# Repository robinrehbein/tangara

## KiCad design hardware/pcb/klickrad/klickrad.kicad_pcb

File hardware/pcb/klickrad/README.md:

# Klickrad-Modul v2 (KiCad 9)

Runde Platine (Ø 32 mm, **0,8 mm** (1,0 mm als Alternative), **2 Lagen**) mit Touch-Rad, kapazitiver Mitteltaste, Guard-Kanal, Haptik-Treiber und Lötpads für den aufgeklebten LRA. Touch-Controller **AT42QT2120** (I²C 0x1C, Wheel-Modus), Haptik **DRV2605L** (0x5A): Schaltung, Elektrodenform und Firmware-Belegung stammen so weit wie möglich von der **Tangara-Faceplate** (cool tech zone). Schnittstelle und Maße folgen `TEILE.md`, Abschnitt „Klickrad-Modul“, mit den unten genannten Abweichungen.

Stand: 2026-10-05, Revision 2 (v1 mit MPR121 bleibt in der git-Historie; 2026-10-05: J1-Footprint, Steckerausrichtung und LRA-Freifläche nach `docs/REVIEW-HAUPTPLATINE.md` K1/H6 geändert, neu geroutet). Erstellt und geprüft mit KiCad 9.0.9 (`kicad-cli`) im Container. **Nichts davon wurde an echter Hardware getestet.**

## Lizenz und Herkunft

Dieses Modul übernimmt Schaltung, Elektrodengeometrie (als Algorithmus), Symbol und Pinbelegung aus der Tangara-Faceplate (`tangara-hw/tangara-faceplate`, `tangara-hw/touchwheel-cover`) von **cool tech zone** (https://cooltech.zone/tangara/), lizenziert unter **CERN-OHL-S-2.0**. Das Modul ist deshalb ebenfalls **CERN-OHL-S-2.0** (Lizenztext: `LICENSE` in diesem Ordner, Kopie aus dem Tangara-Repository; Quellenangabe und Änderungen sind hier und im Schaltplan-Titelblock vermerkt, alle Quelldateien liegen im Repository). Die Firmware-Treiber von Tangara (`touchwheel.cpp`, `haptics.cpp`) sind GPL-3.0 und nicht Teil dieses Ordners.

Quellen: Blogartikel „A Deep Dive Into the Design of Tangara's Touchwheel“ (https://cooltech.zone/tangara/blog/2024-02-07-touchwheel/), „Interpolated Electrode SVG Tool“ (https://cooltech.zone/tangara/labs/touchwheel-electrode-tool/, der Quelltext steht in der Seite), AT42QT2120-Datenblatt (Atmel 9634E–AT42–06/12), Microchip „Capacitive Touch Sensor Design Guide“ DS00002934.

## Übernommen von Tangara / angepasst / neu

| Teil | Status | Tangara-Faceplate | Klickrad v2 |
|---|---|---|---|
| Touch-Controller | **übernommen** | AT42QT2120, VQFN-20 (`VQFN-20-1EP_3x3mm_P0.45mm_EP1.55x1.55mm`), Comms-Modus (MODE an GND), I²C 0x1C, Exposed Pad hier auf GND (Abweichung) | gleich (Symbol aus `faceplate-symbols.kicad_sym`, nur Footprint-/Datenblattfeld ergänzt) |
| Tastenbelegung | **übernommen** | KEY0–2 = Wheel, KEY3 = Mitteltaste, KEY4 = Guard, KEY5–11 unbenutzt | gleich (Firmware-Treiber `touchwheel.cpp` läuft unverändert) |
| Serienwiderstände | **übernommen** (Bauform angepasst) | 10 kΩ 0603 in jeder Elektrodenleitung (R1–R3 Wheel, R5 Taste, R6 Guard) | 10 kΩ **0402** (R1–R3 Wheel, R4 Taste, R5 Guard); Datenblatt 3.1: 4,7 … 20 kΩ |
| Cs-Kondensatoren | **entfällt wie bei Tangara** | keine | keine (Datenblatt: „no external Cs required“) |
| RESET | **übernommen** | R7 10 kΩ nach 3V3 | R6 10 kΩ nach 3V3 |
| CHANGE | **übernommen** | direkt an Stecker, Pull-up in der MCU | direkt an J1 Pin 5 (kein Pull-up auf dem Modul) |
| Entkopplung QT2120 | **übernommen** | 0,1 µF + 1 µF an VDD | C1 0,1 µF + C2 1 µF (0402) |
| DRV2605L | **übernommen** | VSSOP-10, VDD 1 µF, REG 1 µF, IN/TRIG an GND, EN über 10 kΩ nach 3V3, OUT± auf Lötpads | gleich (U2, C3, C4, R7, Lötpads TP1/TP2); EN jetzt wie bei Tangara über 10 kΩ statt fest an 3V3 |
| Wheel-Elektroden | **übernommen, skaliert** | 3 verschachtelte Elektroden (3 Ringe), r = 7,9 … 19,9 mm, Abstand 0,29 mm, Deadzone 2 mm | gleicher Algorithmus (SVG-Tool), r = 6,3 … 12,3 mm (Ringbreite 12 → 6 mm), Abstand 0,25 mm, Deadzone 1,5 mm, Spitzen < 0,2 mm abgerundet |
| Mitteltaste | **übernommen** | kapazitive Scheibe r = 2,5 mm (`qtouch-button`) | gleich, r = 2,5 mm (Ø 5 mm) |
| Guard | **übernommen, angepasst** | Ring r = 22,2 mm, Linie 1 mm, 2,35 mm vom Rad entfernt, über 10 kΩ an KEY4 | ein Kupferpolygon: drei Kreisbögen r = 13,5 … 15,4 mm (wegen der drei Befestigungslöcher geteilt), innen durch zwei schmale Stege (0,2 mm) verbunden, 1 Via, 1,2 mm Abstand zum Rad, über 10 kΩ an KEY4 |
| GND unter dem Rad | **übernommen** | GND-Gitter auf B.Cu (Linie 0,127 mm, Lücke 1,016 mm, 45°), Vorderseite unter dem Rad ohne Kupferfüllung | gleich (Gitter), Vorderseite ohne Füllung |
| Lagenzahl | **übernommen** | 2 Lagen | 2 Lagen, 1,0 mm statt 1,6 mm |
| Wheel-Position 0 / Drehsinn | **übernommen** | 0 oben, steigend gegen den Uhrzeigersinn | gleich, siehe Abschnitt „Wheel-Position“ |
| Abdeckung | **übernommen** | 0,6 mm FR4 mit Siebdruck (`touchwheel-cover`) | KiCad-Projekt `abdeckung/` (Ø 30), Beschriftung MENU / ◄◄ / ►► / ►II |
| I²C-Pull-ups | neu | auf der Hauptplatine | R8/R9 4,7 kΩ, **DNP** |
| 10 µF am DRV2605L | entfällt | – | nicht auf dem Modul (Platzmangel auf 2 Lagen); bei Spannungseinbruch beim LRA 10 µF auf der Hauptplatine nahe dem Stecker ergänzen |
| Stecker | neu | FFC 15-polig (Molex 505278-1533) | **Molex 503480-0600**, FFC/FPC 0,5 mm, 6-polig, Dual Contact, Bauhöhe 1,0 mm, Pin 6 = Reserve; Landmuster wie J21 der Hauptplatine, Kabelmündung nach Süden |
| Rundform, Löcher, LRA-Fläche | neu | Rechteck mit Display | Ø 32, 3 Löcher, LRA-Freifläche 14 × 6 mm für flachen LRA (passt in den Ausschnitt 14 × 10 der Hauptplatine) |
| Display, LCD-Treiber, Backlight | entfällt | JD-T1800, Q1 … | nicht vorhanden |

## Änderungen gegenüber v1

| | v1 | v2 |
|---|---|---|
| Touch-Controller | MPR121 (0x5B), 12 Segmente à 30° | AT42QT2120 (0x1C), 3 Wheel-Elektroden + Taste + Guard |
| Auswertung | Rohwerte → Winkelberechnung in der Firmware | Wheel-Position 0 … 255 direkt vom Chip (Tangara-Treiber) |
| Mitteltaste | SMD-Taster (Omron B3U-1000P) auf J1 Pin 6 | kapazitiv (KEY3, wie Tangara); **J1 Pin 6 ist Reserve und nicht beschaltet** |
| Lagen / Dicke | 4 Lagen, 1,0 mm | **2 Lagen, 0,8 mm** (GND-Gitter auf B.Cu) |
| Stecker | JST-SH 1,0 mm seitlich (>1,5 mm hoch) | **Molex 503480-0600** FFC 0,5 mm, 1,0 mm hoch (Dünnbau, Gerätedicke 8,5 mm) |
| LRA-Fläche | 16 × 6 mm, LRA 3,6 mm hoch | 14 × 6 mm (x −7 … +7, y +3 … +9; in Rev. 2 zuerst 16 × 6), LRA **bis 3,0 mm Höhe**, flache Typen siehe Abschnitt Mechanik |
| Touch-Ring | r = 6,5 … 12,8 mm | r = 6,3 … 12,3 mm; zusätzlich Guard r = 13,5 … 15,4 mm |
| Haptik EN | fest an 3V3 | über 10 kΩ an 3V3 (wie Tangara) |
| Pull-ups | R2/R3 4,7 kΩ (DNP) | R8/R9 4,7 kΩ (DNP); CHANGE-Pull-up entfällt (MCU-intern, wie Tangara) |
| Router | Freerouting | eigener Gitter-Router `tools/route.py` (Freerouting fand keine vollständige Lösung) |
| Abdeckung | nur gedruckt (Ø 30 / Ø 11,6, 1,95 mm) | zusätzlich FR4-Abdeckung 0,6 mm, siehe unten |

## Funktion

| Block | Bauteil | Beschaltung |
|---|---|---|
| Touch-Controller | U1 AT42QT2120 (VQFN-20) | MODE (Pin 10) und VSS an GND, VDD 0,1 µF (C1) + 1 µF (C2), RESET über 10 kΩ (R6) an 3V3, KEY0–2 über je 10 kΩ an die drei Wheel-Elektroden, KEY3 über 10 kΩ an die Mitteltaste, KEY4 über 10 kΩ an den Guard, KEY5–11 offen, CHANGE → J1 Pin 5 |
| Haptik-Treiber | U2 DRV2605LDGSR (VSSOP-10) | VDD (Pin 6, 10) an 3V3 mit 1 µF (C3, wie Tangara), REG 1 µF (C4), IN/TRIG an GND, EN über 10 kΩ (R7) an 3V3, OUT+/OUT− → Lötpads TP1/TP2 |
| Stecker | J1 Molex 503480-0600, FFC/FPC 0,5 mm, 6-polig, Rückseite | siehe unten |
| Pull-ups | R8 (SDA), R9 (SCL) 4,7 kΩ | **DNP**, nur für den Einzeltest des Moduls (Waveshare-Board hat 2,2 kΩ) |

### Pinbelegung J1

| Pin | Signal | Hinweis |
|---|---|---|
| 1 | 3V3 | versorgt AT42QT2120 und DRV2605L |
| 2 | GND | |
| 3 | SDA | |
| 4 | SCL | |
| 5 | CHANGE | AT42QT2120, open drain, aktiv low, **kein Pull-up auf dem Modul** (MCU-interner Pull-up wie bei Tangara, GPIO17 am Waveshare-Board) |
| 6 | (BTN) Reserve | nicht beschaltet. Die Mitteltaste ist kapazitiv (KEY3 des QT2120). Pin bleibt belegt/frei, falls später ein mechanischer Taster nach GND ergänzt wird; KEY3 bleibt dann trotzdem für die Berührung frei. |

### Firmware-Hinweise (aus `tangara-fw/src/drivers/touchwheel.cpp` und `haptics.cpp`)

- Adresse 0x1C. Registerfolge wie Tangara: `RESET` schreiben, 300 ms warten; `SLIDER_OPTIONS = 0xC0` (Wheel an, Keys 0–2); Key-Control KEY0–2 = `0b100` (AKS-Gruppe 1), KEY3 = `0` (Mitteltaste ohne AKS, Software-Entkopplung), KEY4 = `0b10100` (Guard, AKS-Gruppe 1), KEY5–11 = `1` (aus); `RECALIBRATION_DELAY = 0` (Finger nicht wegkalibrieren); `CHARGE_TIME = 0x10`. Status: Bit 7 Kalibrierung, Bit 1 Wheel erkannt (Register `SLIDER_POSITION`), Bit 0 Taste; `KEY_STATUS_A` Bit 3 = Mitteltaste, Bits 0–2 = Wheel berührt.
- Die Mitteltaste liefert **Berührung**, keinen Klick. Der Haptik-Klick (DRV2605L „Strong Click“/„Sharp Click“) wird von der Firmware ausgelöst, wie bei Tangara.
- DRV2605L LRA: Nennspannung `0x46`, Overdrive `0x7B`, Treiberzeit für 235-Hz-LRAs `0b10010000`, geschlossene Regelung, einmalig Auto-Kalibrierung und Ergebnis speichern. Der DRV2605L läuft hier mit EN über 10 kΩ an 3V3, Standby per Register 0x01.

### Wheel-Position (Abstimmung mit der Firmware)

Tangara-Konvention, hier übernommen: **Position 0 = oben, steigend gegen den Uhrzeigersinn**, in Draufsicht auf das Modul (von vorn). „Oben“ ist die Seite gegenüber dem Stecker. Der Stecker J1 liegt bei 270° (unten).

| Position | 0 | 64 | 128 | 192 |
|---|---|---|---|---|
| Richtung (Tangara: up / left / down / right) | oben (90°) | links (180°) | **unten, Stecker-Seite (270°)** | rechts (0°) |

Lage der Elektroden (Maxima der Antwort bei einem Finger auf dem mittleren Radius, Winkel gegen den Uhrzeigersinn ab rechts, von vorn):

| Taste | Elektrode (Pad in `qtouch-wheel`) | Maximum bei |
|---|---|---|
| KEY0 | 1 | 206° (unten links) |
| KEY1 | 2 | 326° (unten rechts) |
| KEY2 | 3 | 86° (oben) |

Herleitung: Die Elektrodenform ist um 120° drehsymmetrisch. Die drei Maxima wurden so gedreht, dass sie an denselben Stellen liegen wie bei der Tangara-Faceplate nach deren Einbaudrehung von −148° (dort Maxima bei 206,3° / 326,3° / 86,3° für KEY0/1/2); damit sind Zuordnung und Drehsinn der Tangara-Firmware (`up = 0`, `left = 64`, `down = 128`, `right = 192` in `input_touch_wheel.cpp`) gültig. **Ungeprüft:** Das ist aus den Footprint-Daten gerechnet (Modell: Überdeckung Finger–Elektrode), nicht gemessen. Falls die Position am echten Rad um einen festen Winkel versetzt ist, in der Firmware einen Offset setzen.

## Elektroden-Geometrie (skaliert von Tangara)

Erzeugt durch `tools/wheel_geometry.py` (Port des Tangara-SVG-Werkzeugs). Parameter von Tangara aus dem Footprint `qtouch-wheel` zurückgerechnet (Flächen 3 × 295 mm², kleinster Abstand 0,29 mm, r = 7,9 … 19,86 mm: innen 8, Breite 12, 3 Ringe, Abstand ≈ 0,3, Deadzone 2).

| Größe | Tangara | Klickrad v2 |
|---|---|---|
| Radius innen / außen | 7,9 / 19,9 mm | 6,3 / 12,3 mm |
| Elektrodenzahl, Ringe | 3, 3 | 3, 3 |
| Abstand zwischen Elektroden | 0,29 mm | 0,25 mm |
| Deadzone | 2 mm | 1,5 mm |
| Fläche je Elektrode | 295 mm² | 87,6 mm² |
| Mitteltaste | r 2,5 mm (19,6 mm²) | r 2,5 mm (19,6 mm²), wie Tangara |
| Guard | Ring r 22,2 mm, 1 mm breit (≈ 140 mm²) | 3 Bögen + Stege r 13,5 … 15,4 mm, 151 mm² (größer als eine Wheel-Elektrode, wie im Datenblatt gefordert) |
| Abstand Rad – Guard | 2,35 mm | 1,2 mm |
| Abstand Rad – Taste | 5,4 mm | 3,8 mm |
| Kleinste Struktur | 0,29 mm | 0,25 mm Abstand, ≥ 0,2 mm Breite |

Das Datenblatt nennt für Wheels „typisch 30 … 50 mm Durchmesser, Segmentbreite typisch 12 mm“. Unser Rad hat 24,6 mm Durchmesser und 6 mm Breite und liegt damit **unter dem typischen Bereich**; ein Modell (Finger als Scheibe, Vektorsumme der drei Elektroden) ergibt für die Winkelauflösung ähnliche Werte wie die Tangara-Geometrie (maximale Abweichung ≈ 12° gegenüber ≈ 14° bei Tangara). **Das ersetzt keinen Test am Rad.**

## Mechanik

- Umriss Ø 32,0 mm, Dicke **0,8 mm** (Bestellung: 0,8 mm; 1,0 mm geht ebenfalls, dann sind Platine und Gerät 0,2 mm dicker und die Touch-Grundkapazität etwas kleiner). Drei Löcher Ø 2,2 mm (NPTH) auf r = 14,6 mm bei 90°, 210°, 330° (wie v1).
- **Stecker J1: Molex 503480-0600** (FFC/FPC 0,5 mm, 6-polig, Easy-On, Dual Contact, 1,0 mm hoch; Molex-Teilenummer bestätigt, DigiKey 5034800600 / 2356622). Lage bei 270° (6-Uhr-Richtung), Mitte bei (0; −10,8) mm, Rückseite. **Footprint (Review K1/H6, geändert):** `lib/Klickrad.pretty/Molex_503480-0600_Hauptplatine` ist das Landmuster von J21 der Hauptplatine (Signalpads 0,3 × 0,7, Nagelpads 0,8 × 1,0 bei x ±2,045, 1,2 mm hinter der Pad-Mitte); der frühere Hirose-FH12-Nachbau (Nagelpads 1,8 × 2,2 bei x ±3,15) ist entfernt. **Ungeprüft:** Nagelpad-Form und -Lage in Y (Molex-Zeichnung SD-503480-001 ist nur als Text lesbar, die Grafik nicht), beide Platinen müssen bei einer Korrektur gemeinsam geändert werden.
  - **Kabelmündung zeigt nach Süden (weg vom Radmittelpunkt)**, Signalpads bei y = −12,8 mm, Nagelpads bei y = −9,6 mm. Vorher (Hirose-Footprint) zeigte die Mündung nach Norden zum Rad; das war falsch: J21 der Hauptplatine hat die Mündung ebenfalls nach Norden (Richtung Klickrad), ein Kabel zwischen zwei nach Norden zeigenden Mündungen bräuchte eine 180°-Haarnadel (Reihenfolge der Adern spiegelt sich, Platz 1,25 … 2,35 mm reicht dafür nicht). Mit Mündung Süden an J1 und Norden an J21 läuft das Kabel **gerade und ungedreht** zwischen beiden: Mündung J1 bei y = −37,8 mm (Hauptplatine-Koordinaten, Rad-Mitte bei −25), Mündung J21 bei −44,2 mm, freie Länge ca. 6,4 mm (frühere Angabe der Hauptplatine „3,5 mm“ galt für eine andere Lage; ungeprüft).
  - **Pin 1 auf Pin 1:** J1 Pin 1 (3V3) liegt in der Ansicht von vorn bei x = +1,25 mm, J21 Pin 1 ebenfalls bei x = +1,25 mm (Ansicht von vorn auf die Hauptplatine). Bei geradem, ungedrehtem Kabel gehen alle sechs Adern auf die gleiche Seitenlage: 1 → 1 (3V3), 2 → 2 (GND), 3 → 3 (SDA), 4 → 4 (SCL), 5 → 5 (CHANGE), 6 → 6 (Reserve). Die Pin-Nummern sind nur Beschriftung (der Stecker hat keine Polung), maßgeblich ist die Seitenlage der Pads: x = +1,25 / +0,75 / +0,25 / −0,25 / −0,75 / −1,25 mm = 3V3 / GND / SDA / SCL / CHANGE / Reserve auf beiden Platinen.
  - **Kabelvariante:** FFC 0,5 mm, 6 Adern, 0,3 mm dick, **gerade und ungedreht** (kein Verdrehen, keine Querfalte, nur ein flacher S-Bogen in der Höhe). Beide Stecker sind Dual Contact (Kontakte oben und unten, Anm. 9 der Zeichnung, nur aus dem Text gelesen): Das Kabel darf an beiden Enden mit den Kontakten nach oben **oder** unten stecken, daher sind **Typ A (Kontakte auf gleicher Seite) und Typ B (Kontakte gegenüber) beide zulässig**; ohne Falte ist Typ A bei beiden Steckern (Kontakte des Kabels zur selben Seite) die naheliegende Wahl. Eine Falte quer zum Kabel oder eine 180°-Drehung vertauscht 1 ↔ 6 und ist **nicht** erlaubt. Abgeleitet aus der Geometrie, **nicht an Hardware geprüft**; vor dem Einschalten Pin für Pin durchklingeln (3V3 an Pin 1 beider Stecker, GND an Pin 2 usw.).
  - **Für den Waveshare-Prototyp:** 6-polige FFC-Breakout-Platine, 0,5 mm Raster, auf 2,54-mm-Stifte (Adapter „FPC 0,5 mm 6P“) und passendes FFC-Kabel 0,5 mm, 6-polig; Pin 1 des Adapters ist ebenfalls zu durchklingeln.
- **LRA-Freifläche** (Rückseite, nur Bauteile gesperrt): x = −7 … +7 mm, y = +3 … +9 mm (**14 × 6 mm**, Mitte 6 mm oberhalb des Radmittelpunkts), für einen LRA **bis 3,0 mm Höhe**, bevorzugt X-Achse. Die Hauptplatine hat dort einen Ausschnitt 14 × 10 mm (Mitte 0 / −19 mm, im Klickrad-Bezug y = +1 … +11): Der LRA muss **höchstens 14 mm lang** sein, sonst stößt er an die Ausschnittkante (Review K-Fund LRA-Freifläche; die Freifläche war zuerst 16 × 6 mm und ist an den Ausschnitt angeglichen, ein größerer Ausschnitt in der Hauptplatine wäre die Alternative). Kandidaten (Maße, Achse und Resonanzfrequenz vor der Bestellung im Datenblatt prüfen; Treiberzeit im DRV2605L passend setzen): Vybronics VL120628H (12 × 6 × 2,0 mm, ca. 200 Hz, laut Koordinator), Vybronics VG0832022D (Tangaras BOM-Empfehlung, Maße ungeprüft), 4,5 × 12 × 3,0 (235 Hz) aus `TEILE.md`. Der 8 × 15 × 3,0-LRA (170 Hz) aus `TEILE.md` ist mit 15 mm **zu lang** für den Ausschnitt 14 × 10 und entfällt (ohne Änderung der Hauptplatine). Ein 10 × 10 × 1,0-LRA (Vybronics VLV101040J) braucht y = +1 … +11 und passt wegen der Widerstände R3 … R5 bei y ≈ 0 … 1 **nicht** in diese Revision (nicht umgesetzt). Lötpads TP1 (LRA+) und TP2 (LRA−) liegen **auf der Ostseite** bei x = +13,1 mm, y = −2,4 / −4,8 mm (v1: westlich bei x = −12,3): U2 sitzt östlich, die LRA-Leitungen sind so kurz; die Litzen müssen im CAD zur Ostseite geführt werden. Unter dem LRA liegen das GND-Gitter, Leiterbahnen und Vias unter Lötstopplack.
- Bauteile auf der Rückseite: 0402-Teile 0,5 mm, U1 VQFN 0,85 mm (nominal), **U2 DRV2605L im VSSOP-10 ca. 1,1 mm** und J1 1,0 mm liegen **über der Vorgabe 0,8 mm** (J1 innerhalb der Stecker-Vorgabe ≤ 1,2 mm). Das DSBGA-9-Gehäuse (DRV2605LYZFR, 0,5 mm Raster, ca. 0,6 mm hoch, bei TI als lieferbar gelistet) wäre flacher, wurde aber nicht umgesetzt (Hand- und Routingaufwand; ungeprüft). Vorderseite: nur Kupferflächen unter Lötstopplack, keine Bauteile.
- Bauteilpositionen für CAD: `fertigung/bauteilpositionen.csv` (Bezug Platinenmitte, mm, y nach oben in der Ansicht von vorn).
- **Guard und Schrauben:** Die Guard-Bögen halten 2,2 mm Abstand zur Lochmitte (Schraubenkopf Ø 3,5, Abdeckungstasche Ø 4,0), sie reichen bis r = 15,4 mm, also 0,4 mm über den Rand der Abdeckung (Ø 30) hinaus.
- **Änderungsbedarf in `TEILE.md` / CAD** (nicht Teil dieses Auftrags, deshalb hier gemeldet): 2 statt 4 Lagen; Touch-Ring r = 6,3 … 12,3 mm plus Guard r = 13,5 … 15,4 mm; Mitteltaste kapazitiv statt SMD-Taster (Höhenvorgabe ≤ 1,5 mm entfällt, die Mitteltaste-Kappe Ø 11,0 und das Loch Ø 11,6 in der Abdeckung entfallen); Stecker Pin 5 = CHANGE, Pin 6 = Reserve; I²C-Adresse 0x1C; Wheel-Positions-Konvention.

### Abdeckung: gedruckt (1,95 mm) oder FR4 (0,6 mm)?

Tangara deckt das Rad mit einer 0,6 mm dicken FR4-Platte ab (`touchwheel-cover`: nur Umriss und Siebdruck, kein Kupfer).

- **Gedruckte Abdeckung 1,95 mm passt formal:** Das Datenblatt erlaubt für Wheels/Slider „bis 3 mm Kunststoff“. Sie ist aber mehr als dreimal so dick wie Tangaras 0,6 mm, und unser Rad ist nur halb so breit. Das Signal wird kleiner und weicher. Zusätzlich darf zwischen Platine und Abdeckung **keine Luft** liegen (dünnes doppelseitiges Klebeband 0,05 … 0,1 mm vollflächig; gedruckt mit 100 % Füllung, glatte Seite zur Platine). Mit Druckabdeckung die Schwellen (DTHR-Register 16 … 27) senken und `CHARGE_TIME` prüfen.
- **Empfehlung: FR4-Abdeckung mitbestellen** (`abdeckung/`, wenige Euro, gleiche Platinenfertiger), als erste Wahl für den Prototyp, die gedruckte Abdeckung als Rückfall. Die FR4-Abdeckung ist eben, gleichmäßig dick, hat Siebdruck-Beschriftung und entspricht dem bei Tangara erprobten Aufbau. Aufkleben mit demselben dünnen Klebeband.
- Folge für die Mechanik: Die Oberfläche liegt mit 0,6 mm um **1,35 mm tiefer** als mit der gedruckten Abdeckung. Der Distanzring bzw. die Frontöffnung im CAD (Parameter `E_COVER_T`, `COVER_T`) muss angepasst werden, sonst sitzt das Rad zu tief.

`abdeckung/klickrad-abdeckung.kicad_pcb`: Ø 30 mm, ohne Mittenloch, drei Aussparungen r = 2,1 mm um die Schraubenköpfe der Platine (r = 14,6 mm bei 90°/210°/330°). Siebdruck (F.SilkS): Kreis Ø 11,6 mm (Mitteltaste), Kreis r = 12,4 mm (Außenkante des Rads), „MENU“ oben, ◄◄ links, ►► rechts, ►II unten (Konvention des iPod nano), „v2“. Bestellung: 2 Lagen, **0,6 mm**, ohne Kupfer (beide Lagen leer), Lötstopplack und Siebdruck nach Wunsch (z. B. schwarz/weiß), `abdeckung/fertigung/klickrad_abdeckung_gerber.zip`. Orientierung: oben = Seite gegenüber dem Stecker.

## Lagenaufbau (2 Lagen, Begründung)

Die Tangara-Faceplate ist 2-lagig (1,6 mm, F.Cu und B.Cu, geprüft in `tangara-faceplate.kicad_pcb`), obwohl sie ein 40-mm-Rad trägt. Das gleiche Prinzip genügt hier:

| Lage | Inhalt |
|---|---|
| F.Cu | Wheel (3 Elektroden), Mitteltaste, Guard (3 Bögen); sonst nur wenige kurze Leiterbahnen im Innenring r = 3,65 … 6,15 mm zwischen Taste und Rad (Prüfskript `tools/pruefe_vorderseite.py`) |
| B.Cu | alle Bauteile, Leiterbahnen, **GND-Gitter** (Linie 0,127 mm, Lücke 1,016 mm, 45°, Glättung 2, wie bei Tangara) |

Gründe für 2 statt 4 Lagen: (1) Es gibt nur 6 Durchkontaktierungen zur Vorderseite (3 Wheel, Taste, Guard 3 Bögen = 7 Vias); die Verdrahtung der 20 Netze passt auf die Rückseite, weil der AT42QT2120 nur 5 Tasten verdrahtet und keine Referenzwiderstände braucht (MPR121 v1: REXT, VREG, 12 Elektroden). (2) Die Touch-Flächen brauchen unten eine möglichst unbelegte Masse, das Gitter bei Tangara ist erprobt. (3) Zwei Lagen sind billiger und überall bestellbar.

**Ungeprüft:** Abstand zwischen Elektroden und GND-Gitter ist bei 1,0 mm Dicke kleiner als bei Tangaras 1,6 mm (Grundkapazität höher, Empfindlichkeit etwas geringer). Die Wirkung wurde nicht gemessen. Notfalls das Gitter unter dem Rad ausdünnen (größere Lücke) oder die Schwellen senken.

## Bestückung (Handlötung)

1. Platine mit der Vorderseite auf die Heizplatte oder vorheizen (100 … 120 °C), Rückseite oben.
2. **U1 AT42QT2120 (VQFN-20, 0,45 mm, Exposed Pad 1,55 mm, auf GND):** Paste dünn auftragen (Schablone aus dem Paste-Layer oder Spritze), Pin 1 nach der Silkscreen-Marke, Heißluft ca. 240 … 250 °C. Danach Brücken mit Flussmittel entfernen. Flussmittel-Reste anschließend gründlich reinigen (Datenblatt 3.3: Rückstände stören die Touch-Messung).
3. **U2 DRV2605L (VSSOP-10):** Pin 1 nach der Dreiecksmarke, Schlepplöten oder wie U1.
4. 0402-Teile mit Paste. R8/R9 **nicht** bestücken (DNP).
5. J1 zuletzt, wenig Hitze; die Montagefüße (MP) gut anlöten.
6. Messen: 3V3 gegen GND auf Kurzschluss prüfen, 3V3 anlegen, per I²C auf 0x1C und 0x5A antworten lassen.
7. LRA mit doppelseitigem Klebeband in die markierte Freifläche kleben, Litzen an TP1/TP2 löten.
8. Abdeckung aufkleben (siehe oben).

## Bestellung

`fertigung/klickrad_v2_gerber_jlcpcb.zip` (für JLCPCB) und `fertigung/klickrad_v2_gerber_pcbway.zip` (für PCBWay, identischer Inhalt): Gerber X2 (Protel-Endungen) mit Bohrdaten PTH/NPTH, Paste-Lagen für eine Schablone und `.gbrjob`. Alle Daten, Gerber, Bohrungen und Bestückungsdatei, haben den Ursprung in der Platinenmitte.

| Einstellung | Wert |
|---|---|
| Lagen | 2 |
| Dicke | **0,8 mm** (Alternative 1,0 mm) |
| Maße | rund, Ø 32 mm (Umriss ist ein Kreis auf Edge.Cuts) |
| Kupfer | 1 oz |
| Oberfläche | ENIG empfohlen (ebene Pads für das 0,45-mm-VQFN), bleifreies HASL geht auch |
| Via | 0,6 / 0,3 mm, Tenting (Standard) |
| Lötstopplack | Farbe frei; die Touch-Flächen sind absichtlich **ohne Öffnung** |
| Platinen | 5 Stück Mindestmenge |

Kleinste Strukturen: Leiterbahn 0,15 mm, Abstand 0,15 mm (DRC-Mindestwert 0,127 mm), Elektrodenabstand 0,25 mm, GND-Gitter 0,127 mm, Bohrung 0,3 mm, Randabstand Kupfer 0,3 mm.

Bestückung durch den Hersteller ist nicht vorgesehen. Stückliste: `klickrad_bom.csv` (alle Spalten), `fertigung/klickrad_v2_bom_jlcpcb.csv` (JLCPCB-Format), `fertigung/klickrad_v2_cpl_jlcpcb.csv` (Bestückungsdatei, **Drehwinkel der Gehäuse nicht gegen den JLCPCB-Bibliothekswinkel geprüft**). LCSC-Nummern wurden am 2026-10-04 auf lcsc.com bestätigt; **AT42QT2120-MMH (C617900) war dort nicht auf Lager**, Alternativen: Mouser/DigiKey (ca. 5 USD).

## Was geprüft ist und was nicht

Geprüft (mit `kicad-cli` 9.0.9):

- **ERC** (`kicad-cli sch erc`): 0 Fehler, 0 Warnungen (nach der J1-Umstellung 2026-10-05 wiederholt).
- **DRC** (`kicad-cli pcb drc --schematic-parity --all-track-errors`) auf der fertigen `klickrad.kicad_pcb` (nach der J1-Umstellung und dem Neuverlegen 2026-10-05 wiederholt): 0 Fehler, 0 nicht verbundene Anschlüsse, Schaltplan-Abgleich ohne Abweichung (die Meldung `net_conflict` zu U1 Pad 21 ist die bekannte Warnung wegen des GND-Exposed-Pads). Es bleiben 5 Warnungen `courtyards_overlap` (C1/C2, R8/R9 und U1 mit R3/R4/R5): Die Kondensator- und Widerstandspaare sitzen absichtlich dicht (0402, Pads berühren sich nur im gleichen Netz bzw. mit >= 0,127 mm Abstand), die Courtyards der 0402-Teile sind größer als nötig. Löten und Bestücken von Hand bleibt möglich, kein elektrischer Fehler.
- Rechnerprüfung `tools/pruefe_vorderseite.py`: alle Vorderseiten-Leiterbahnen liegen innerhalb des Rings, keine außerhalb.
- **Neu verlegt 2026-10-05:** `tools/route_order.txt` jetzt mit GND an erster Stelle (sonst blieben drei GND-Inseln ohne Anbindung); ein Via-Paar (3V3/SDA bei x +3,4 … +3,95, y −3,15 … −3,65) wurde von Hand um 0,12 mm auseinandergezogen (Bohrabstand 0,44 statt 0,5 mm), ebenfalls in `tools/routed.kicad_pcb`. Die Leiterbahnen wurden nur über DRC und Bildansicht geprüft.
- Gerber-ZIPs für JLCPCB und PCBWay, Abdeckung (Gerber-ZIP), Schaltplan-PDF, Vorschaubilder und 3D-Renderings wurden erzeugt; das Gerber-Bild wurde nicht in einem fremden Viewer (z. B. Hersteller-Vorschau) gegengeprüft.
- Das Exposed Pad von U1 (Pad 21) liegt auf GND und ist mit den freien Pins 8/10 verbunden (**Abweichung von Tangara**, wo es unbeschaltet bleibt; Datenblatt-Empfehlung ungeprüft).
- Die letzte offene Verbindung des Routers (SCL an U1 Pin 14) wurde von Hand gezogen und GND-Stummel wurden von Hand entfernt, danach DRC wiederholt.

Nicht geprüft:

- **Keine Hardware gebaut oder gemessen.** Touch-Empfindlichkeit, Winkelauflösung, Wheel-Nullpunkt und Drehsinn, Störungen durch den LRA, Haptik-Kalibrierung, Verhalten mit gedruckter Abdeckung: offen.
- Das Rad liegt unter der typischen Größe des Datenblatts (24,6 mm statt 30 … 50 mm, Ringbreite 6 mm statt 12 mm).
- Footprints der Standardbibliothek (VSSOP-10, VQFN-20, 0402/0603) und der Molex-503480-Footprint J1 (Landmuster von J21, Nagelpads 0,8 × 1,0 geschätzt, Zeichnungsgrafik nicht lesbar) wurden nicht gegen die Herstellerzeichnungen vermessen. Das Exposed Pad von U1 liegt auf GND (anders als bei Tangara).
- Höhen von U1/U2/J1 aus dem Datenblatt bzw. aus dem Gedächtnis.
- Der Router (`tools/route.py`) ist eigener Code; die Leiterbahnen wurden nur über DRC und Bildansicht geprüft; SCL an U1 Pin 14 ist von Hand ergänzt. Einige Bahnen laufen länger als nötig. Die Guard-Verbindung läuft als lange Bahn über die Rückseite; sie liegt nicht unter den Elektroden einer anderen Funktion, ihre Länge wurde nicht bewertet.
- Das GND-Gitter erzeugt Kupferinseln; deren Warnungen siehe oben.
- Stromaufnahme: Der LRA wird aus der 3V3-Schiene des Waveshare-Boards versorgt, deren Belastbarkeit ungeprüft ist. Spannungseinbruch bei der Auto-Kalibrierung beobachten.
- **Pin 1 ↔ Pin 1 und Kabelführung (gerade, ungedreht, Mündungen gegenläufig) sind aus der Geometrie von Hauptplatine und Klickrad abgeleitet, nicht mit einem echten Kabel und Stecker geprüft.** Ob die Mündung des echten Molex-503480 wirklich auf der Seite der Signalpads liegt, folgt aus dem Footprint der Hauptplatine (Zeichnungsgrafik nicht lesbar) und ist **ungeprüft**; stimmt es nicht, wäre J1 um 180° zu drehen (Pin-1-Lage dann ebenfalls prüfen). CPL-Drehung von J1 (0°, Bottom) ist nicht gegen die JLCPCB-Konvention geprüft; J1 wird ohnehin von Hand bestückt.
- LCSC-Verfügbarkeit und Preise (Stand 2026-10-04, U1 nicht auf Lager).

## Neu erzeugen

Voraussetzungen: KiCad 9 (Python-Modul `pcbnew`, `kicad-cli`), Python-Pakete `shapely`, `numpy`, `scipy`, `Pillow`; `rsvg-convert` für PNG-Vorschauen.

```sh
python3 tools/make_lib.py                 # lib/Klickrad.pretty (Touch-Flächen, Loch), lib/Klickrad.kicad_sym (AT42QT2120)
SKIPROUTE=1 tools/make.sh                 # abgegebene Platine neu füllen und beschriften (ohne Router)
tools/make.sh                             # komplette Neuberechnung inkl. Router (dauert mehrere Minuten, Ergebnis kann abweichen; GND steht in route_order.txt vorn)
tools/export.sh                           # Schaltplan, ERC/DRC-Berichte, Gerber, Positionsdatei, Vorschau, Stückliste, Abdeckung
python3 tools/pruefe_vorderseite.py       # F.Cu-Prüfung
```

| Ordner/Datei | Inhalt |
|---|---|
| `klickrad.kicad_pro/.kicad_sch/.kicad_pcb` | KiCad-Projekt |
| `lib/Klickrad.pretty`, `lib/Klickrad.kicad_sym`, `fp-lib-table`, `sym-lib-table` | eigene Footprints/Symbol, Bibliothekstabellen; der Molex-Footprint `Molex_503480-0600_Hauptplatine` ist eine Kopie aus der Hauptplatine und wird von `make_lib.py` nicht erzeugt |
| `tools/` | Python-Skripte; `netlist.py` ist die einzige Quelle für Bauteile und Netze, `wheel_geometry.py` für die Elektroden, `placement.py` für die Platzierung, `route.py`/`route_loop.py` für die Verdrahtung |
| `tools/routed.kicad_pcb` | Platzierung + Routing-Ergebnis, Ausgangspunkt für `SKIPROUTE=1` |
| `abdeckung/` | KiCad-Projekt der FR4-Abdeckung, `fertigung/` (Gerber-ZIP), `vorschau/` |
| `fertigung/` | Gerber-ZIPs (JLCPCB, PCBWay), Bohrdaten, Bauteilpositionen, JLCPCB-BOM und -CPL |
| `vorschau/` | SVG/PNG von Vorderseite, Rückseite, Kupfer, 3D-Ansichten, Schaltplan als PNG und PDF |
| `pruefung/` | ERC- und DRC-Bericht |
| `klickrad_bom.csv` | Stückliste |
| `LICENSE` | CERN-OHL-S-2.0 |

Der Schaltplan wird per Skript erzeugt und ist übersichtlich, aber nicht von Hand gezeichnet; Änderungen am besten in `tools/netlist.py` und `tools/gen_sch.py` machen und neu erzeugen, nicht im Editor.

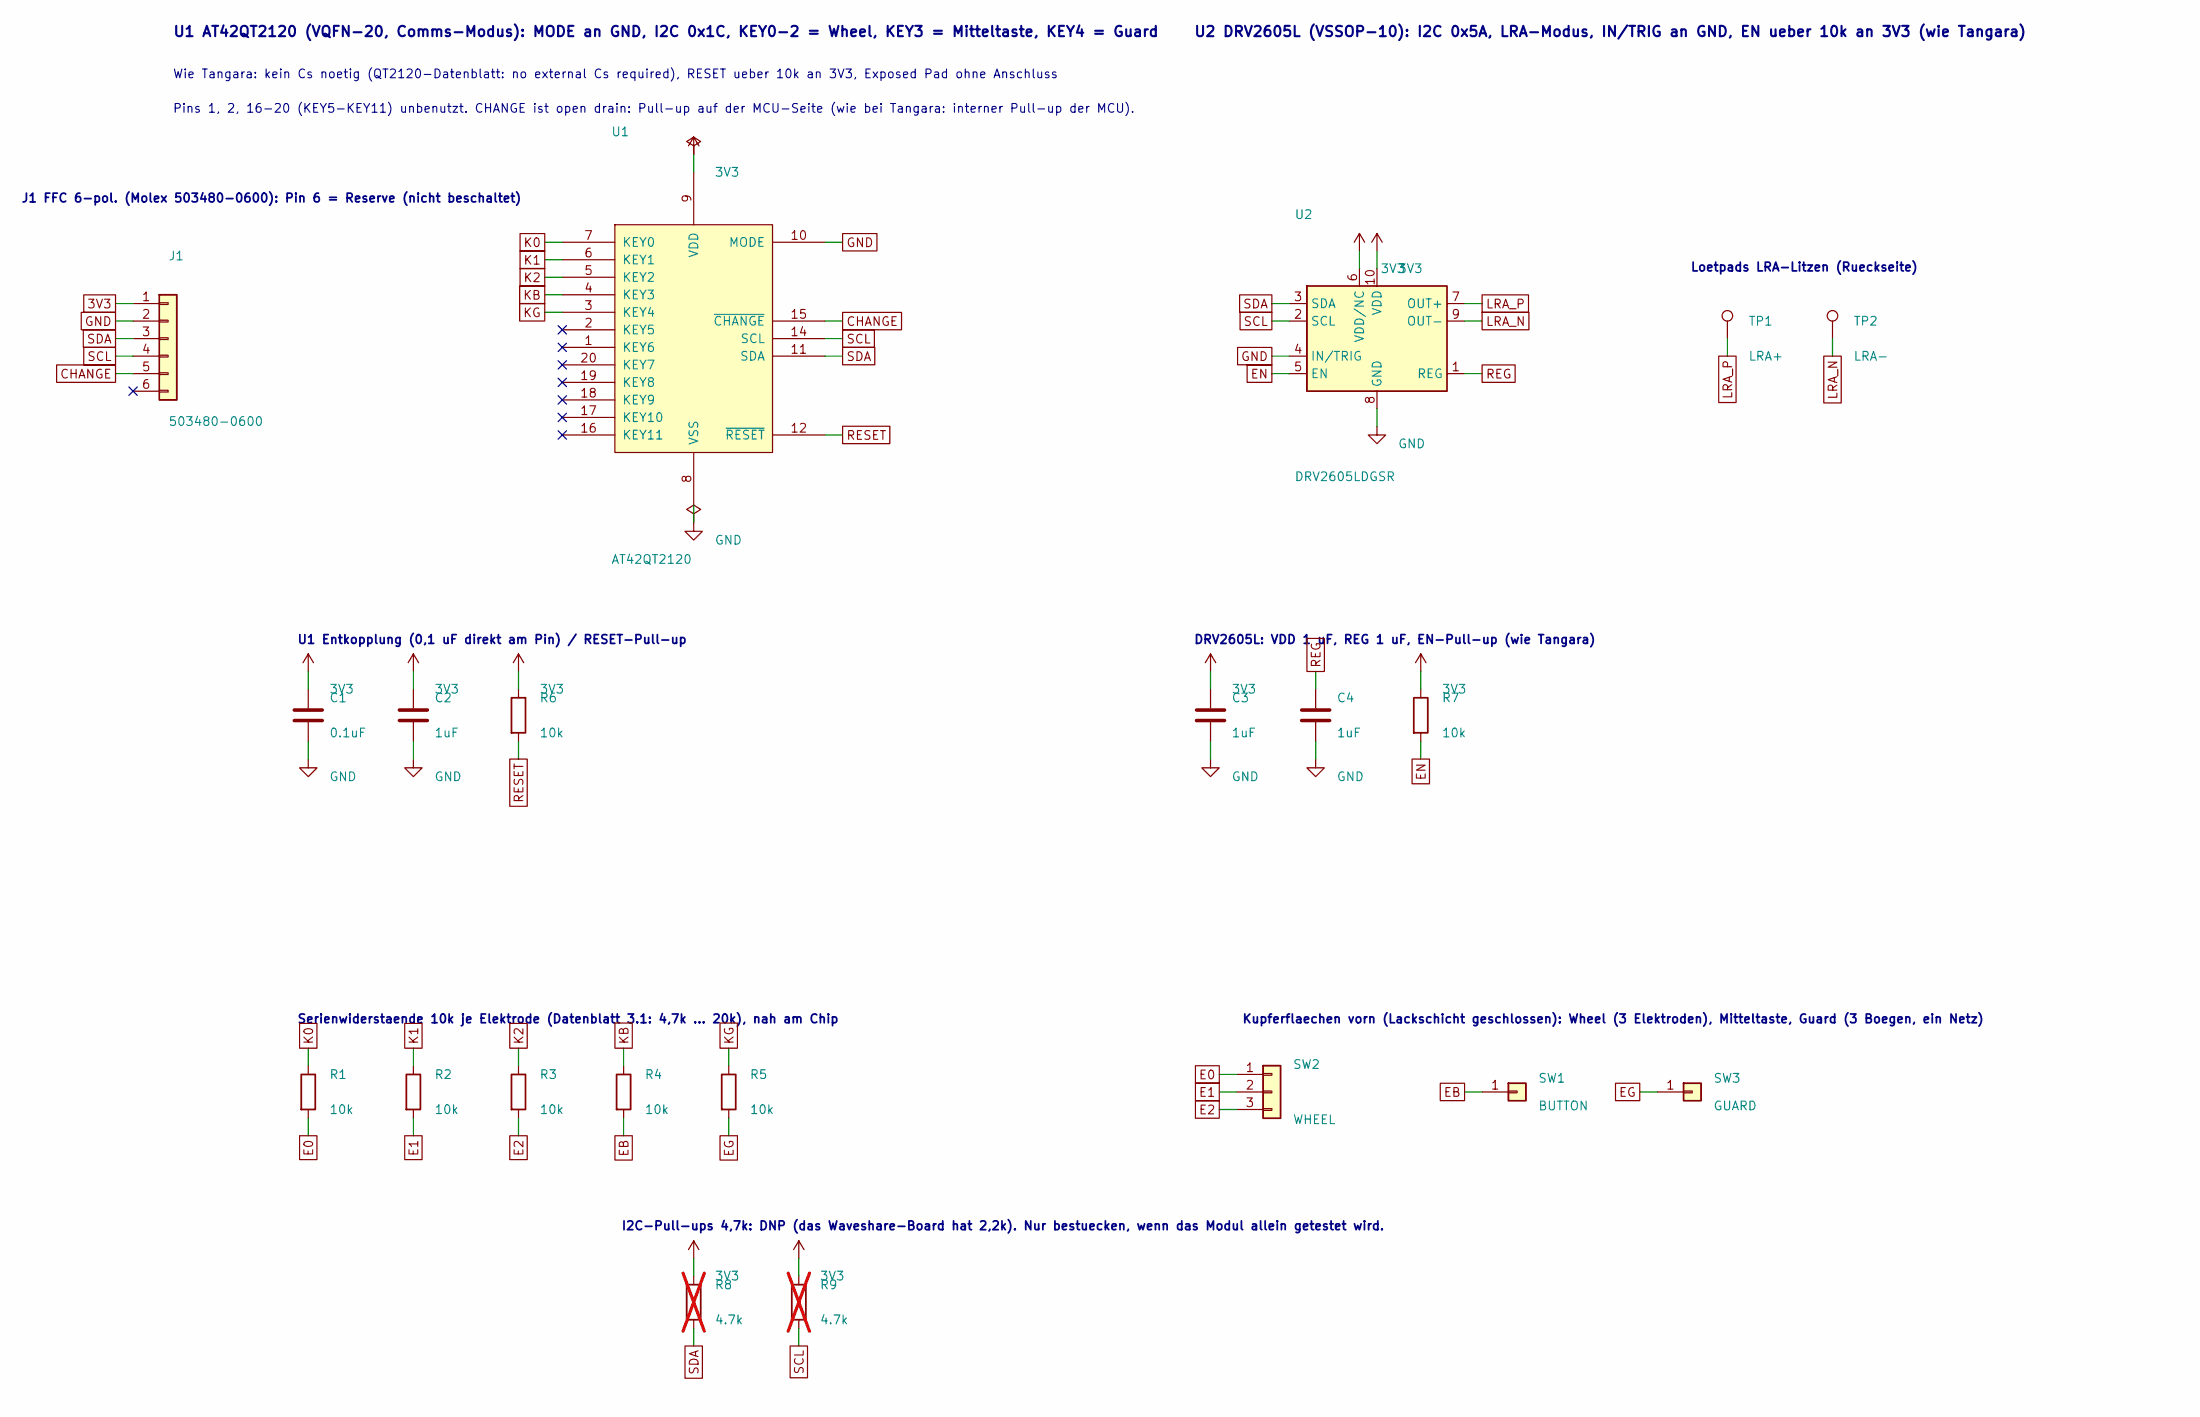
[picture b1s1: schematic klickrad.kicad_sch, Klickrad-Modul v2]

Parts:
C1: 0.1uF; C_0402_1005Metric
C2, C3, C4: 1uF; C_0402_1005Metric
J1: 503480-0600; Molex_503480-0600_Hauptplatine; MPN 503480-0600
R1, R2, R3, R4, R5, R6, R7: 10k; R_0402_1005Metric
R8, R9: 4.7k; R_0402_1005Metric; not fitted
SW1: BUTTON; qtouch-button
SW2: WHEEL; qtouch-wheel
SW3: GUARD; qtouch-guard
TP1: LRA+; SolderWirePad_1x01_SMD_1x2mm
TP2: LRA-; SolderWirePad_1x01_SMD_1x2mm
U1: AT42QT2120; VQFN-20-1EP_3x3mm_P0.45mm_EP1.55x1.55mm; MPN AT42QT2120-MMH
U2: DRV2605LDGSR; VSSOP-10_3x3mm_P0.5mm; MPN DRV2605LDGSR

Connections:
3V3: C1.1, C2.1, C3.1, J1.1, R6.1, R7.1, R8.1, R9.1, U1.9 (VDD), U2.6 (VDD/NC), U2.10 (VDD)
CHANGE: J1.5, U1.15 (~CHANGE)
E0: R1.2, SW2.1
E1: R2.2, SW2.2
E2: R3.2, SW2.3
EB: R4.2, SW1.1
EG: R5.2, SW3.1
EN: R7.2, U2.5 (EN)
GND: C1.2, C2.2, C3.2, C4.2, J1.2, U1.8 (VSS), U1.10 (MODE), U1.21, U2.4 (IN/TRIG), U2.8 (GND)
K0: R1.1, U1.7 (KEY0)
K1: R2.1, U1.6 (KEY1)
K2: R3.1, U1.5 (KEY2)
KB: R4.1, U1.4 (KEY3)
KG: R5.1, U1.3 (KEY4)
LRA_N: TP2.1, U2.9 (OUT-)
LRA_P: TP1.1, U2.7 (OUT+)
REG: C4.1, U2.1 (REG)
RESET: R6.2, U1.12 (~RESET)
SCL: J1.4, R9.2, U1.14 (SCL), U2.2 (SCL)
SDA: J1.3, R8.2, U1.11 (SDA), U2.3 (SDA)

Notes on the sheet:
U1 AT42QT2120 (VQFN-20, Comms-Modus): MODE an GND, I2C 0x1C, KEY0-2 = Wheel, KEY3 = Mitteltaste, KEY4 = Guard
Wie Tangara: kein Cs noetig (QT2120-Datenblatt: no external Cs required), RESET ueber 10k an 3V3, Exposed Pad ohne Anschluss
Pins 1, 2, 16-20 (KEY5-KEY11) unbenutzt. CHANGE ist open drain: Pull-up auf der MCU-Seite (wie bei Tangara: interner Pull-up der MCU).
U1 Entkopplung (0,1 uF direkt am Pin) / RESET-Pull-up
Serienwiderstaende 10k je Elektrode (Datenblatt 3.1: 4,7k ... 20k), nah am Chip
Kupferflaechen vorn (Lackschicht geschlossen): Wheel (3 Elektroden), Mitteltaste, Guard (3 Boegen, ein Netz)
J1 FFC 6-pol. (Molex 503480-0600): Pin 6 = Reserve (nicht beschaltet)
U2 DRV2605L (VSSOP-10): I2C 0x5A, LRA-Modus, IN/TRIG an GND, EN ueber 10k an 3V3 (wie Tangara)
DRV2605L: VDD 1 uF, REG 1 uF, EN-Pull-up (wie Tangara)
Loetpads LRA-Litzen (Rueckseite)
I2C-Pull-ups 4,7k: DNP (das Waveshare-Board hat 2,2k). Nur bestuecken, wenn das Modul allein getestet wird.

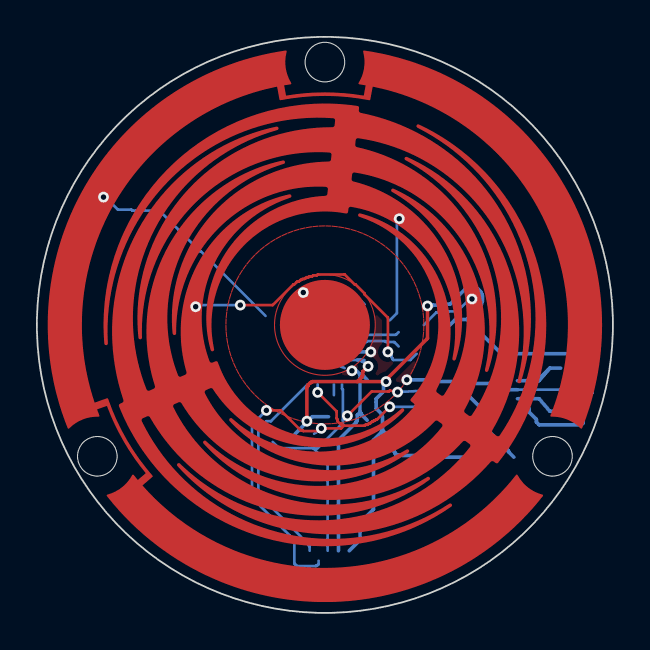
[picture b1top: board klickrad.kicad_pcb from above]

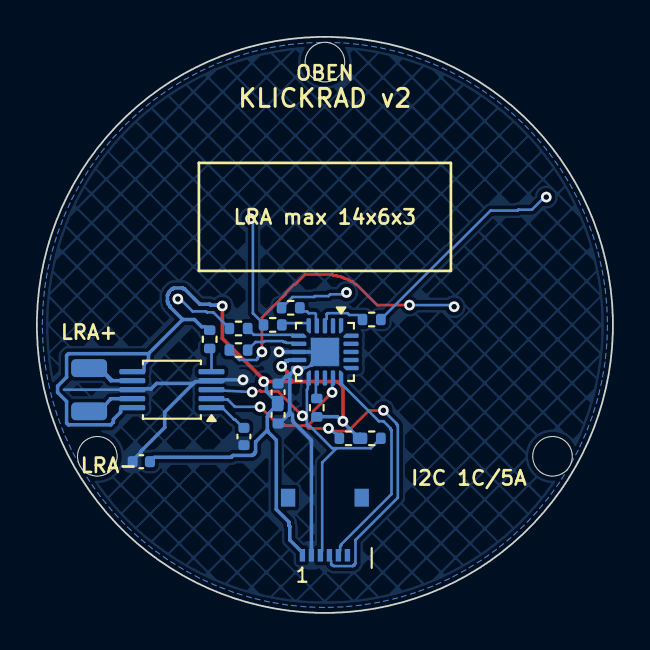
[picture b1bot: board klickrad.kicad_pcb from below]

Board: 2 copper layers, 32.0 x 32.0 mm, 24 parts (18 on the bottom side), 20 nets.

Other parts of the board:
H1, H2, H3: M2; MountingHole_2.2mm_NPTH

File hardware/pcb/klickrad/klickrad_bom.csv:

Referenzen,Anzahl,Wert,Footprint,Hersteller,Herstellerteilenummer,LCSC,Bestückung,Höhe_mm,Hinweis
J1,1,503480-0600,Molex_503480-0600_Hauptplatine,Molex,503480-0600,,ja,"1,0","FFC/FPC 6-pol., 0,5 mm, Easy-On, Dual Contact (Kabel Typ A und B), Bauhöhe 1,0 mm; DigiKey 5034800600 (2356622), Mouser, Newark; LCSC-Nummer NICHT geprüft"
U1,1,AT42QT2120,VQFN-20-1EP_3x3mm_P0.45mm_EP1.55x1.55mm,Microchip,AT42QT2120-MMH,C617900,ja,"0,85","VQFN-20 3x3 mm, 0,45 mm; Nummer bestätigt, bei LCSC am 2026-10-04 NICHT auf Lager -> Mouser/DigiKey (ca. 5 USD)"
U2,1,DRV2605LDGSR,VSSOP-10_3x3mm_P0.5mm,Texas Instruments,DRV2605LDGSR,C527464,ja,"ca. 1,1",VSSOP-10
C1,1,0.1uF,C_0402_1005Metric,Samsung,CL05B104KO5NNNC,C1525,ja,"0,5","X7R 16 V, 0402"
"C2, C3, C4",3,1uF,C_0402_1005Metric,Samsung,CL05A105KA5NQNC,C52923,ja,"0,5","X5R 6,3 V, 0402"
"R1, R2, R3, R4, R5, R6, R7",7,10k,R_0402_1005Metric,UNI-ROYAL,0402WGF1002TCE,C25744,ja,"0,4","1 %, 0402; am 2026-10-04 auf lcsc.com bestätigt (Tangara: 0603)"
"R8, R9",2,4.7k,R_0402_1005Metric,UNI-ROYAL,0402WGF4701TCE,C25900,DNP (nicht bestücken),"0,4","1 %, 0402, nur DNP-Option"
"TP1, TP2",2,LRA+/LRA-,SolderWirePad_1x01_SMD_1x2mm,,,,Pads (kein Bauteil),0,Lötpads für die LRA-Litzen
SW1-SW3,3,Touch,Klickrad:qtouch-button/-wheel/-guard,,,,Kupferfläche (kein Bauteil),0,"Mitteltaste, Wheel (3 Elektroden), Guard"
(extern),1,"FR4-Abdeckung 0,6 mm",abdeckung/klickrad-abdeckung,,,,"optional, separat bestellen","0,6",Gerber: abdeckung/fertigung
(extern),1,LRA (X-Achse),,,,,"aufkleben, Litzen an TP1/TP2",,nicht Teil der Platine; Typ und Maße siehe TEILE.md und Einkaufsliste

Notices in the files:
hardware/pcb/hauptplatine/README.md:
Quelle: Tangara-Hardware Rev. 5 (cool tech zone, CERN-OHL-S-2.0, ), Netzliste in `quellen/tangara_netlist_rev5.json`. Anzahl = Bauteile der Stückliste (ohne Testpunkte und Bohrungen); gesamt 139 Bauteile in 72 Positionen.
- Dieses Design ist ein abgeleitetes Werk der **Tangara-Hardware** (cool tech zone, jacqueline, , Quelle ), lizenziert unter **CERN-OHL-S-2.0**; es steht daher ebenfalls unter CERN-OHL-S-2.0 (Datei `LICENSE`).
- Standardfootprints und -symbole: KiCad-Bibliotheken (CC-BY-SA 4.0 mit Ausnahme für Designs).
